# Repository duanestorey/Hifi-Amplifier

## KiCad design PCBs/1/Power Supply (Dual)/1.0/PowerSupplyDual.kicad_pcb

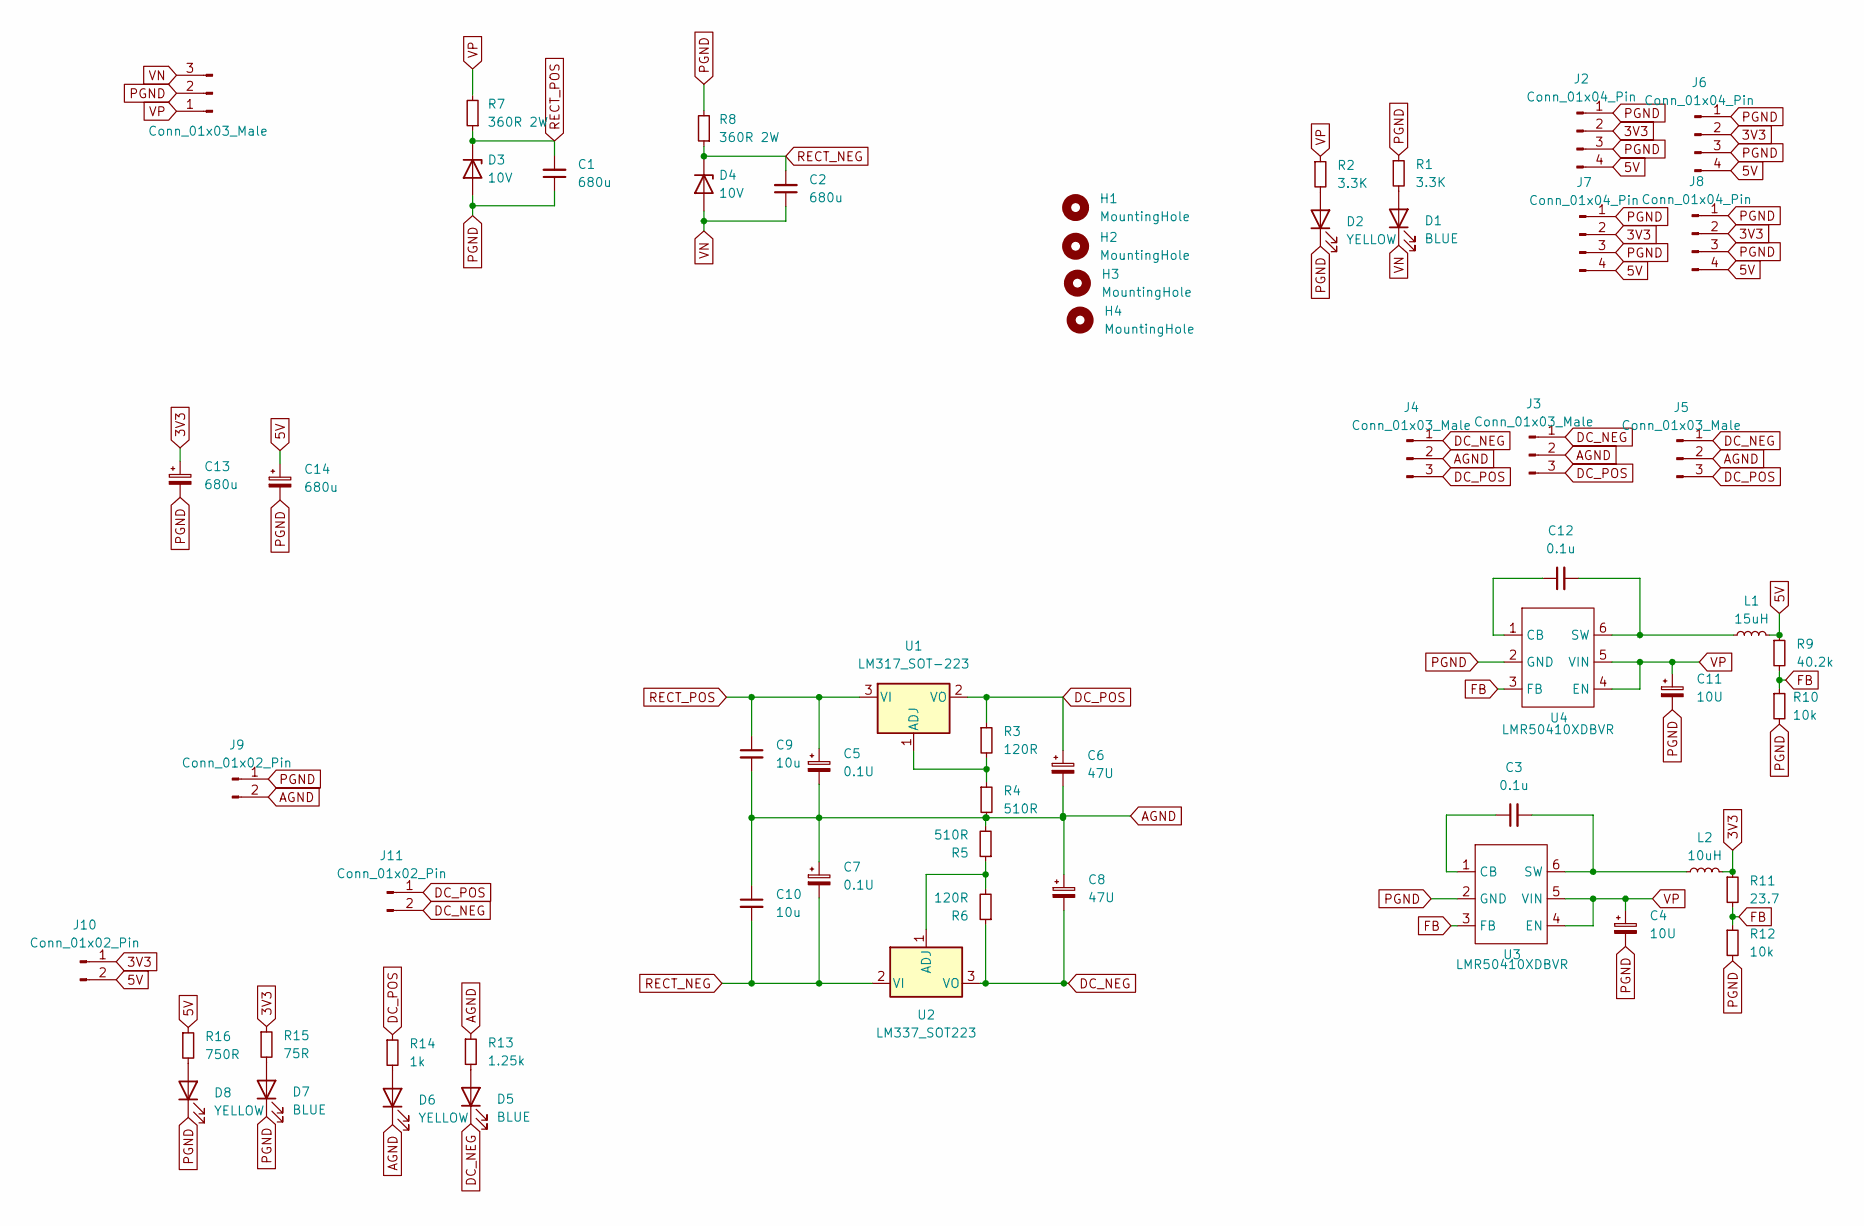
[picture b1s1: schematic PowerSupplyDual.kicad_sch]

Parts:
C1, C2, C13, C14: 680u; CP_Radial_D8.0mm_P5.00mm
C3, C12: 0.1u; C_0805_2012Metric_Pad1.18x1.45mm_HandSolder
C4, C11: 10U; C_1206_3216Metric_Pad1.33x1.80mm_HandSolder
C5, C7: 0.1U; C_0603_1608Metric_Pad1.08x0.95mm_HandSolder
C6, C8: 47U; C_1206_3216Metric_Pad1.33x1.80mm_HandSolder
C9, C10: 10u; C_1206_3216Metric_Pad1.33x1.80mm_HandSolder
D1, D5, D7: BLUE; LED_0805_2012Metric_Pad1.15x1.40mm_HandSolder
D2, D6, D8: YELLOW; LED_0805_2012Metric_Pad1.15x1.40mm_HandSolder
D3, D4: 10V; D_DO-41_SOD81_P10.16mm_Horizontal
H1, H2, H3, H4: MountingHole; MountingHole_3.2mm_M3
J1: Conn_01x03_Male; JST_VH_B3P-VH_1x03_P3.96mm_Vertical
J2, J6, J7, J8: Conn_01x04_Pin; JST_XH_B4B-XH-A_1x04_P2.50mm_Vertical
J3, J4, J5: Conn_01x03_Male; JST_PH_B3B-PH-K_1x03_P2.00mm_Vertical
J9: Conn_01x02_Pin; JST_XH_B2B-XH-A_1x02_P2.50mm_Vertical
J10, J11: Conn_01x02_Pin; PinHeader_1x02_P2.54mm_Vertical
L1: 15uH; L_Taiyo-Yuden_NR-60xx_HandSoldering
L2: 10uH; L_Taiyo-Yuden_NR-60xx_HandSoldering
R1, R2: 3.3K; R_0603_1608Metric_Pad0.98x0.95mm_HandSolder
R3, R6: 120R; R_0603_1608Metric_Pad0.98x0.95mm_HandSolder
R4, R5: 510R; R_0603_1608Metric_Pad0.98x0.95mm_HandSolder
R7, R8: 360R 2W; R_Axial_DIN0411_L9.9mm_D3.6mm_P15.24mm_Horizontal
R9: 40.2k; R_0603_1608Metric_Pad0.98x0.95mm_HandSolder
R10, R12: 10k; R_0603_1608Metric_Pad0.98x0.95mm_HandSolder
R11: 23.7; R_0603_1608Metric_Pad0.98x0.95mm_HandSolder
R13: 1.25k; R_0603_1608Metric_Pad0.98x0.95mm_HandSolder
R14: 1k; R_0603_1608Metric_Pad0.98x0.95mm_HandSolder
R15: 75R; R_0603_1608Metric_Pad0.98x0.95mm_HandSolder
R16: 750R; R_0603_1608Metric_Pad0.98x0.95mm_HandSolder
U1: LM317_SOT-223; SOT-223-3_TabPin2
U2: LM337_SOT223; SOT-223-3_TabPin2
U3, U4: LMR50410XDBVR; SOT-23-6_Handsoldering

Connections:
3V3: C13.1, J2.2, J6.2, J7.2, J8.2, J10.1, L2.2, R11.1, R15.1
5V: C14.1, J2.4, J6.4, J7.4, J8.4, J10.2, L1.2, R9.1, R16.1
AGND: C5.2, C6.2, C7.1, C8.1, C9.2, C10.1, D6.1 (K), J3.2, J4.2, J5.2, J9.2, R4.2, R5.2, R13.1
DC_NEG: C8.2, D5.1 (K), J3.1, J4.1, J5.1, J11.2, R6.1, U2.3 (VO)
DC_POS: C6.1, J3.3, J4.3, J5.3, J11.1, R3.1, R14.1, U1.2 (VO)
FB: R9.2, R10.1, R11.2, R12.1, U3.3 (FB), U4.3 (FB)
unnamed: D1.2 (A), R1.2
unnamed: D2.2 (A), R2.2
unnamed: D5.2 (A), R13.2
unnamed: D6.2 (A), R14.2
unnamed: D7.2 (A), R15.2
unnamed: D8.2 (A), R16.2
unnamed: R3.2, R4.1, U1.1 (ADJ)
unnamed: R5.1, R6.2, U2.1 (ADJ)
unnamed: C3.1, U3.1 (CB)
unnamed: C3.2, L2.1, U3.6 (SW)
unnamed: C12.1, U4.1 (CB)
unnamed: C12.2, L1.1, U4.6 (SW)
PGND: C1.1, C4.2, C11.2, C13.2, C14.2, D2.1 (K), D3.2 (A), D7.1 (K), D8.1 (K), J1.2, J2.1, J2.3, J6.1, J6.3, J7.1, J7.3, J8.1, J8.3, J9.1, R1.1, R8.2, R10.2, R12.2, U3.2 (GND), U4.2 (GND)
RECT_NEG: C2.2, C7.2, C10.2, D4.1 (K), R8.1, U2.2 (VI)
RECT_POS: C1.2, C5.1, C9.1, D3.1 (K), R7.1, U1.3 (VI)
VN: C2.1, D1.1 (K), D4.2 (A), J1.3
VP: C4.1, C11.1, J1.1, R2.1, R7.2, U3.4 (EN), U3.5 (VIN), U4.4 (EN), U4.5 (VIN)

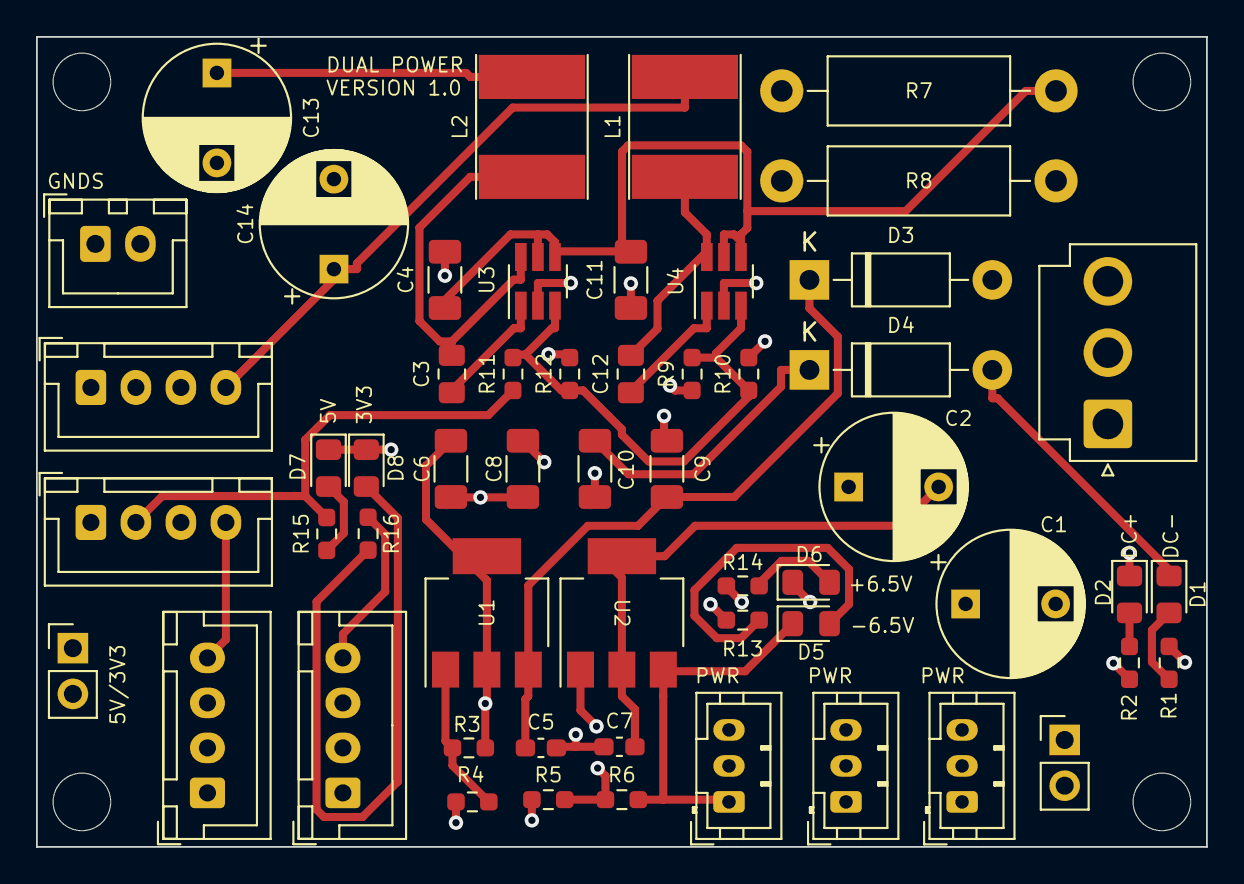
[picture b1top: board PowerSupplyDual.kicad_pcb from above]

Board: 4 copper layers, 65.0 x 45.0 mm, 59 parts (0 on the bottom side), 23 nets.

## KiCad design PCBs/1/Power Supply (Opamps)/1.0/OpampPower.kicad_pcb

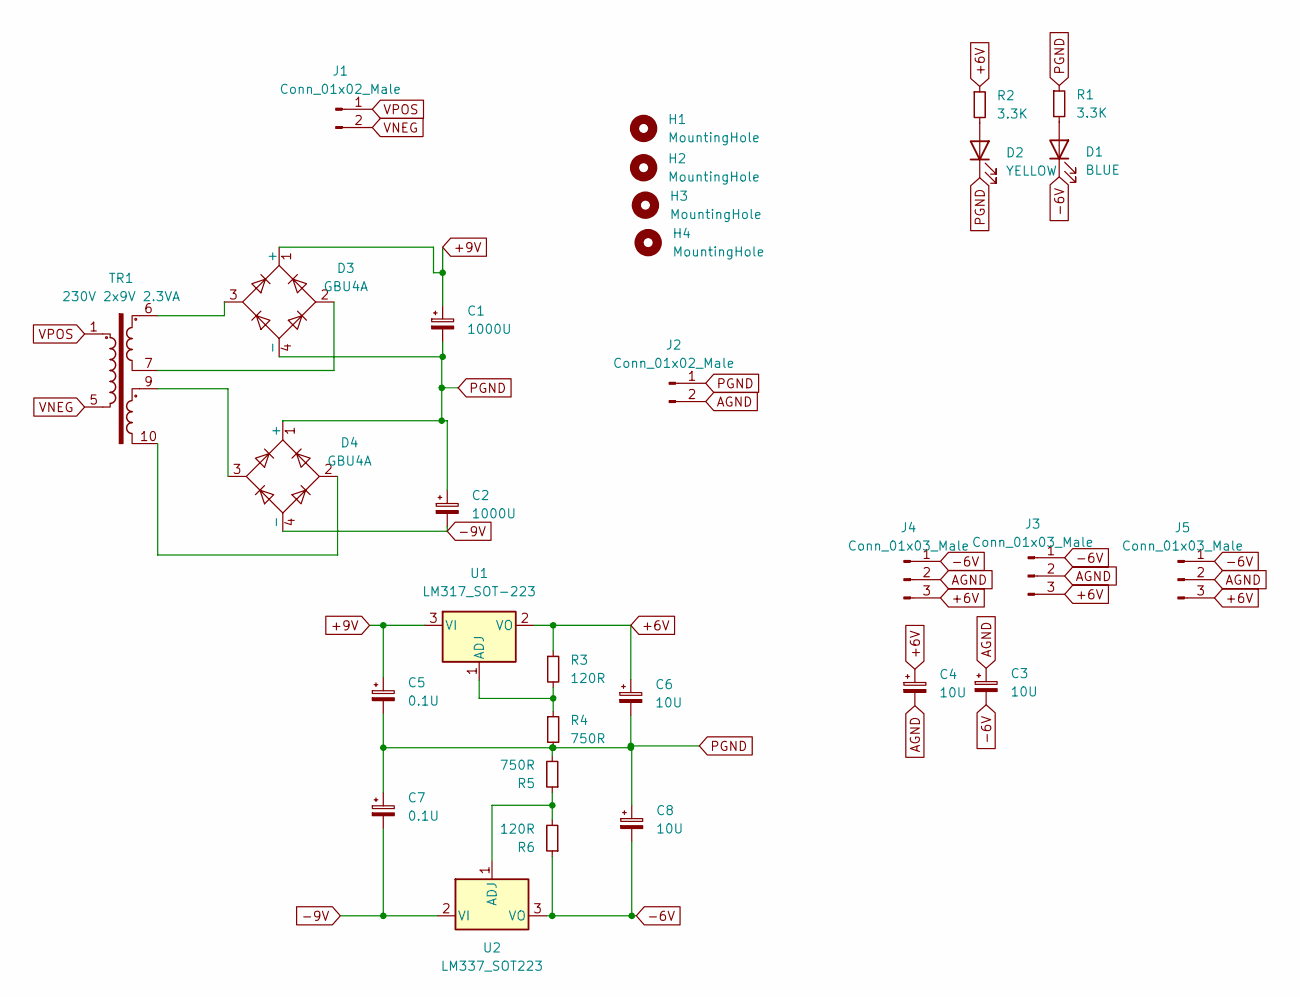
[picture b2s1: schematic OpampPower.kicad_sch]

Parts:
C1, C2: 1000U; CP_Radial_D10.0mm_P5.00mm_P7.50mm
C3, C4, C6, C8: 10U; C_1206_3216Metric_Pad1.33x1.80mm_HandSolder
C5, C7: 0.1U; C_0603_1608Metric_Pad1.08x0.95mm_HandSolder
D1: BLUE; LED_0805_2012Metric_Pad1.15x1.40mm_HandSolder
D2: YELLOW; LED_0805_2012Metric_Pad1.15x1.40mm_HandSolder
D3, D4: GBU4A; Diode_Bridge_Vishay_GBU
H1, H2, H3, H4: MountingHole; MountingHole_3.2mm_M3
J1: Conn_01x02_Male; JST_XH_B2B-XH-A_1x02_P2.50mm_Vertical
J2: Conn_01x02_Male; JST_PH_B2B-PH-K_1x02_P2.00mm_Vertical
J3, J4, J5: Conn_01x03_Male; JST_PH_B3B-PH-K_1x03_P2.00mm_Vertical
R1, R2: 3.3K; R_0603_1608Metric_Pad0.98x0.95mm_HandSolder
R3, R6: 120R; R_0805_2012Metric_Pad1.20x1.40mm_HandSolder
R4, R5: 750R; R_0805_2012Metric_Pad1.20x1.40mm_HandSolder
TR1: 230V 2x9V 2.3VA; Transformer_Breve_TEZ-28x33
U1: LM317_SOT-223; SOT-223-3_TabPin2
U2: LM337_SOT223; SOT-223-3_TabPin2

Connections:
+6V: C4.1, C6.1, J3.3, J4.3, J5.3, R2.1, R3.1, U1.2 (VO)
+9V: C1.1, C5.1, D3.1 (+), U1.3 (VI)
-6V: C3.2, C8.2, D1.1 (K), J3.1, J4.1, J5.1, R6.1, U2.3 (VO)
-9V: C2.2, C7.2, D4.4 (-), U2.2 (VI)
AGND: C3.1, C4.2, J2.2, J3.2, J4.2, J5.2
unnamed: D1.2 (A), R1.2
unnamed: D2.2 (A), R2.2
unnamed: D3.2, TR1.7
unnamed: D3.3, TR1.6
unnamed: D4.2, TR1.10
unnamed: D4.3, TR1.9
unnamed: R3.2, R4.1, U1.1 (ADJ)
unnamed: R5.1, R6.2, U2.1 (ADJ)
PGND: C1.2, C2.1, C5.2, C6.2, C7.1, C8.1, D2.1 (K), D3.4 (-), D4.1 (+), J2.1, R1.1, R4.2, R5.2
VNEG: J1.2, TR1.5
VPOS: J1.1, TR1.1

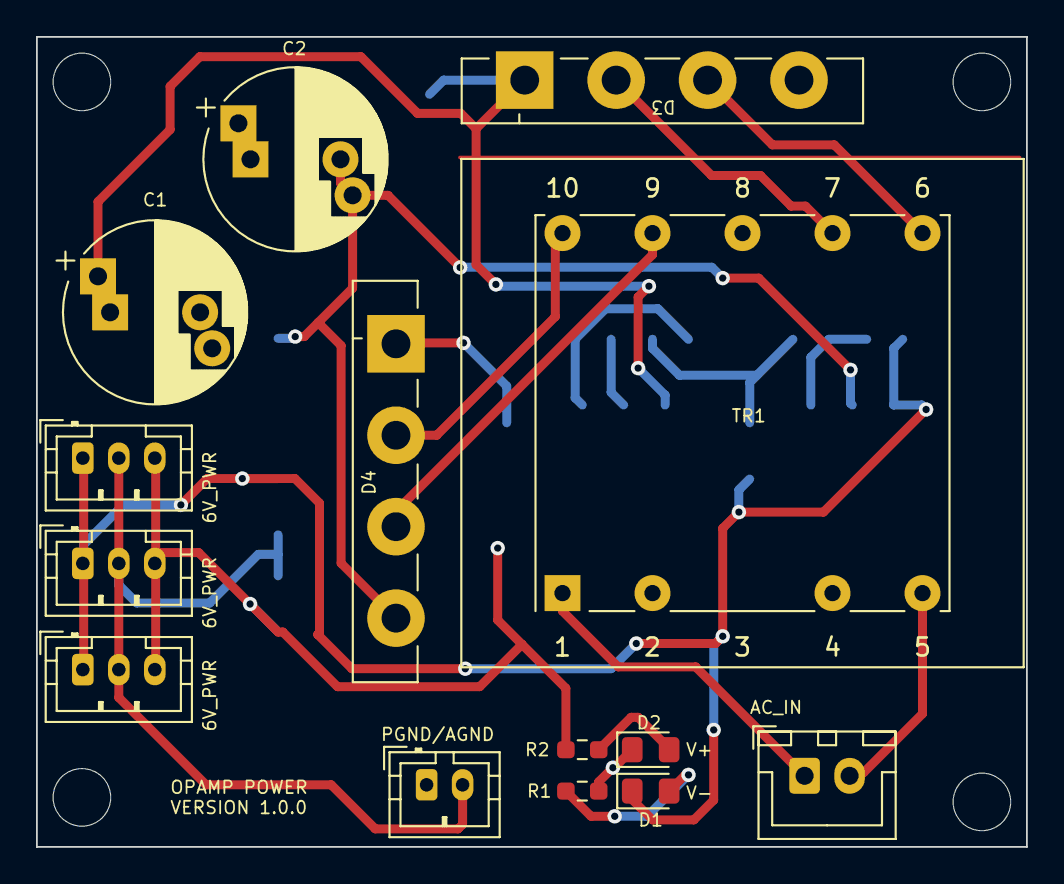
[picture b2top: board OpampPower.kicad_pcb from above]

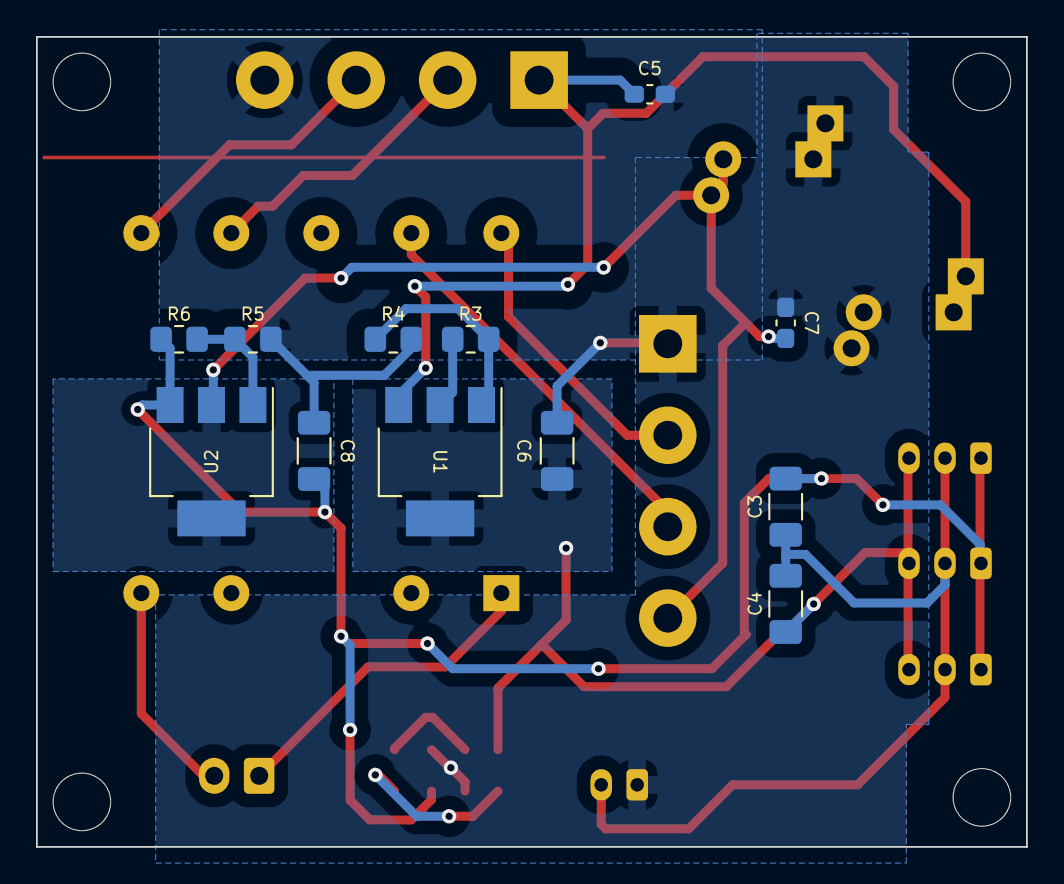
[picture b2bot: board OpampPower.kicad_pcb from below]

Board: 2 copper layers, 55.0 x 45.0 mm, 30 parts (12 on the bottom side), 16 nets.

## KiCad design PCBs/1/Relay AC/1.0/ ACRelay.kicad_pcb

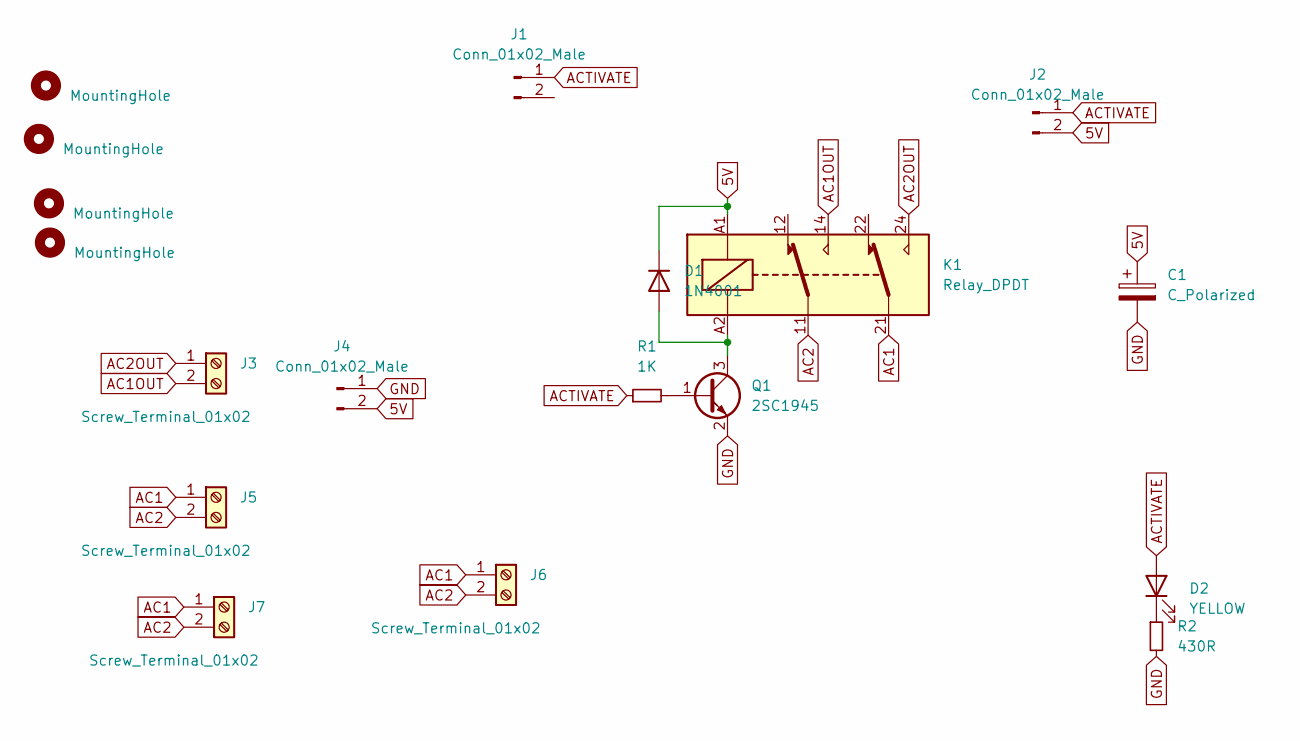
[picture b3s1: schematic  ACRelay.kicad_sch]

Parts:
C1: C_Polarized; CP_Radial_D6.3mm_P2.50mm
D1: 1N4001; D_SMA
D2: YELLOW; D_0805_2012Metric_Pad1.15x1.40mm_HandSolder
H1, H2, H3, H4: MountingHole; MountingHole_3.2mm_M3
J1, J4: Conn_01x02_Male; JST_PH_B2B-PH-K_1x02_P2.00mm_Vertical
J2: Conn_01x02_Male; PinHeader_1x02_P2.54mm_Vertical
J3, J5, J6, J7: Screw_Terminal_01x02; JST_XH_B2B-XH-A_1x02_P2.50mm_Vertical
K1: Relay_DPDT; Relay_DPDT_Omron_G2RL-2
Q1: 2SC1945; SOT-23_Handsoldering
R1: 1K; R_0603_1608Metric
R2: 430R; R_0603_1608Metric_Pad0.98x0.95mm_HandSolder

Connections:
5V: C1.1, D1.1 (K), J2.2, J4.2, K1.A1
AC1: J5.1, J6.1, J7.1, K1.21
AC1OUT: J3.2, K1.14
AC2: J5.2, J6.2, J7.2, K1.11
AC2OUT: J3.1, K1.24
ACTIVATE: D2.2 (A), J1.1, J2.1, R1.1
GND: C1.2, J4.1, Q1.2 (E), R2.2
unnamed: D1.2 (A), K1.A2, Q1.3 (C)
unnamed: D2.1 (K), R2.1
unnamed: Q1.1 (B), R1.2

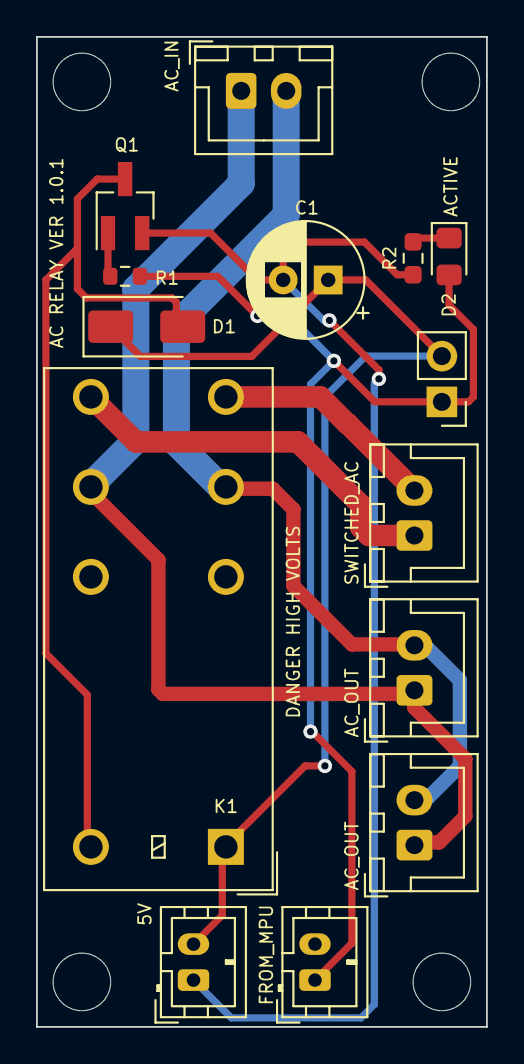
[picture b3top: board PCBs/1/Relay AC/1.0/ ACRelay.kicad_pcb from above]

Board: 2 copper layers, 25.0 x 55.0 mm, 18 parts (0 on the bottom side), 10 nets.

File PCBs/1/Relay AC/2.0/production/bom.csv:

Designator,Footprint,Quantity,Value,LCSC Part #
C1,CP_Radial_D6.3mm_P2.50mm,1,C_Polarized,
D1,D_SMA,1,1N4001,
D2,D_0805_2012Metric_Pad1.15x1.40mm_HandSolder,1,YELLOW,
"H1, H2, H3, H4",MountingHole_3.2mm_M3,4,MountingHole,
"J1, J4",JST_PH_B2B-PH-K_1x02_P2.00mm_Vertical,2,Conn_01x02_Male,
J2,PinHeader_1x02_P2.54mm_Vertical,1,Conn_01x02_Male,
"J3, J5, J6, J7",JST_XH_B2B-XH-A_1x02_P2.50mm_Vertical,4,Screw_Terminal_01x02,
Q1,SOT-23_Handsoldering,1,2SC1945,
R1,R_0603_1608Metric,1,1K,
R2,R_0603_1608Metric_Pad0.98x0.95mm_HandSolder,1,430R,
RL1,Relay_DPDT_Omron_G2RL,1,G2RL-2-ASI-DC5,

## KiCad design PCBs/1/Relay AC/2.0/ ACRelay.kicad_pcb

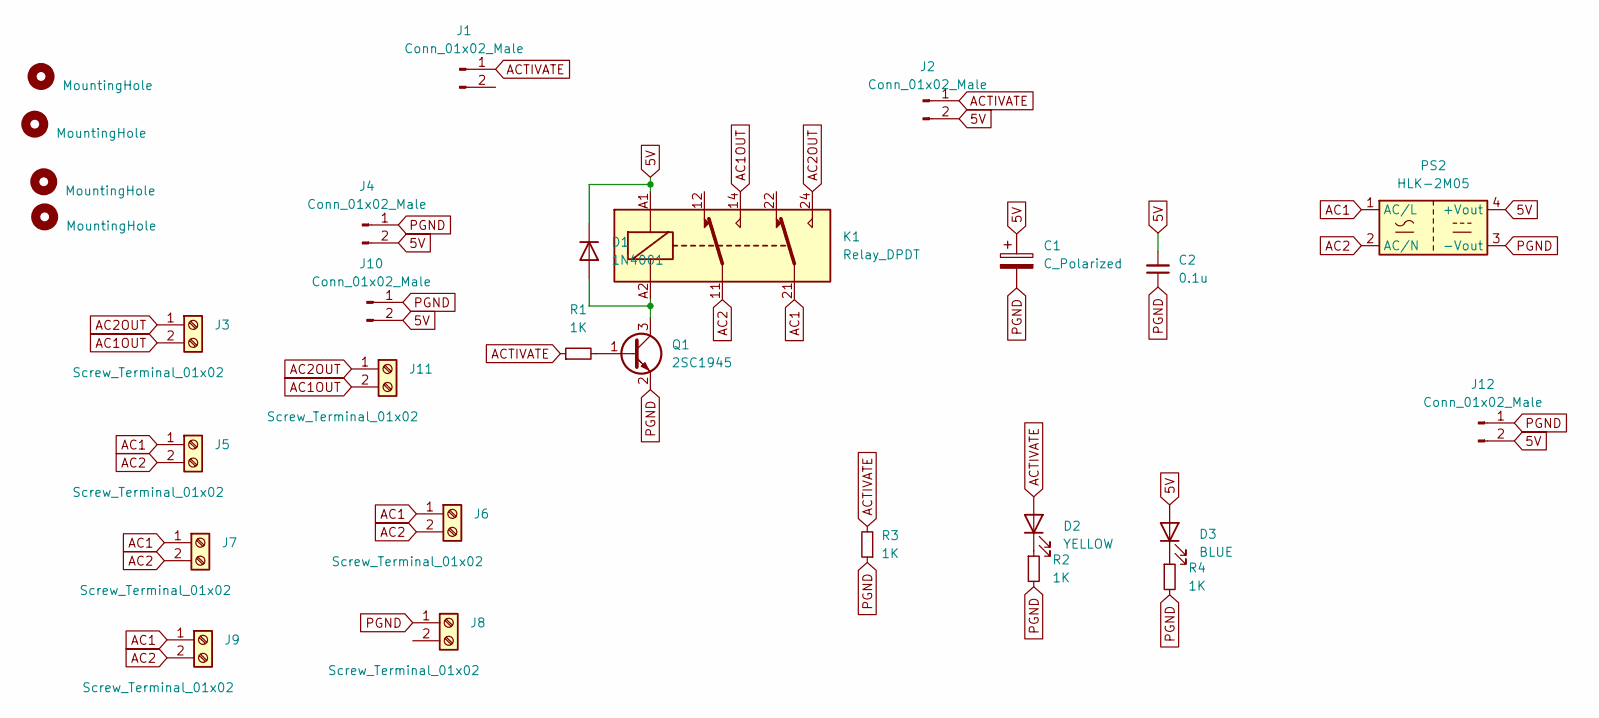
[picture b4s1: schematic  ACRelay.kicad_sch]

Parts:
C1: C_Polarized; CP_Radial_D8.0mm_P2.50mm
C2: 0.1u; C_0805_2012Metric_Pad1.18x1.45mm_HandSolder
D1: 1N4001; D_SMA
D2: YELLOW; D_0805_2012Metric_Pad1.15x1.40mm_HandSolder
D3: BLUE; D_0805_2012Metric_Pad1.15x1.40mm_HandSolder
H1, H2, H3, H4: MountingHole; MountingHole_3.2mm_M3
J1, J4, J10: Conn_01x02_Male; JST_PH_B2B-PH-K_1x02_P2.00mm_Vertical
J2, J12: Conn_01x02_Male; PinHeader_1x02_P2.54mm_Vertical
J3, J5, J6, J7, J8, J9, J11: Screw_Terminal_01x02; JST_XH_B2B-XH-A_1x02_P2.50mm_Vertical
K1: Relay_DPDT; Relay_DPDT_Omron_G2RL-2
PS2: HLK-2M05
Q1: 2SC1945; SOT-23_Handsoldering
R1, R3: 1K; R_0603_1608Metric
R2, R4: 1K; R_0603_1608Metric_Pad0.98x0.95mm_HandSolder

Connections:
5V: C1.1, C2.2, D1.1 (K), D3.2 (A), J2.2, J4.2, J10.2, J12.2, K1.A1, PS2.4 (+Vout)
AC1: J5.1, J6.1, J7.1, J9.1, K1.21, PS2.1 (AC/L)
AC1OUT: J3.2, J11.2, K1.14
AC2: J5.2, J6.2, J7.2, J9.2, K1.11, PS2.2 (AC/N)
AC2OUT: J3.1, J11.1, K1.24
ACTIVATE: D2.2 (A), J1.1, J2.1, R1.1, R3.2
unnamed: D1.2 (A), K1.A2, Q1.3 (C)
unnamed: D2.1 (K), R2.1
unnamed: D3.1 (K), R4.1
unnamed: Q1.1 (B), R1.2
PGND: C1.2, C2.1, J4.1, J8.1, J10.1, J12.1, PS2.3 (-Vout), Q1.2 (E), R2.2, R3.1, R4.2

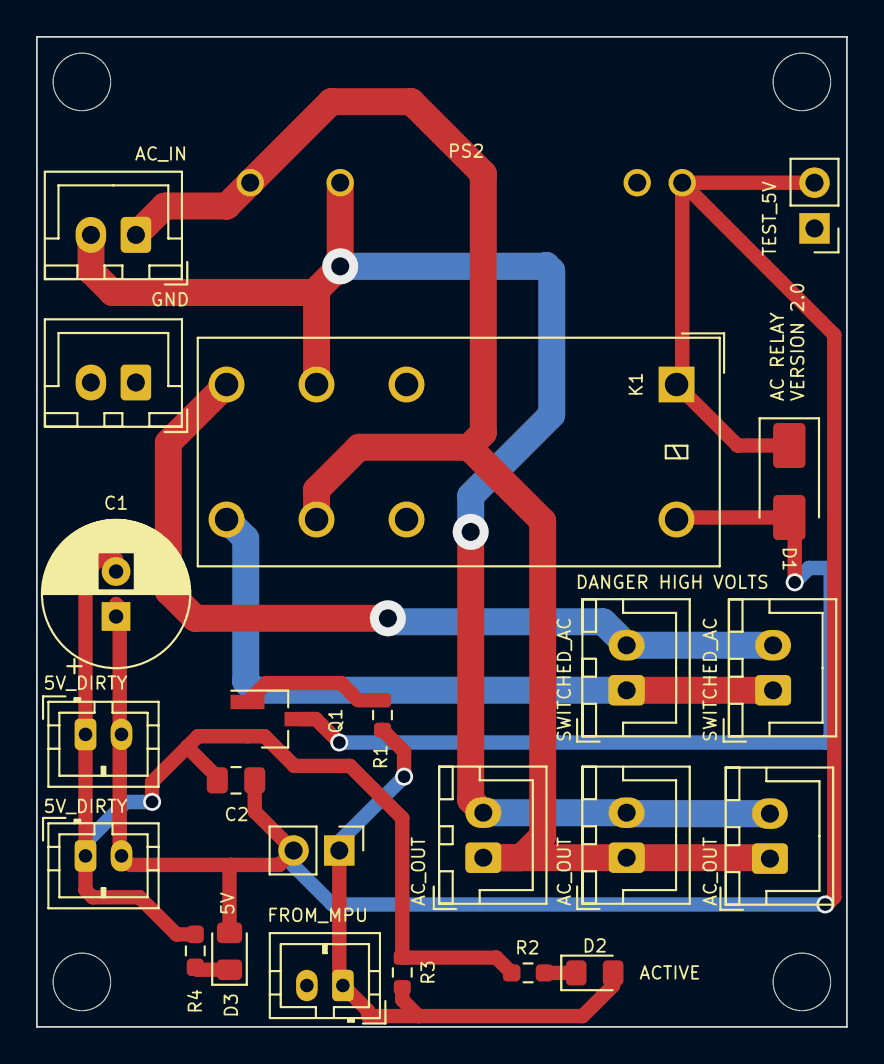
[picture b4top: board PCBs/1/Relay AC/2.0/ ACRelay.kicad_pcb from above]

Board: 2 copper layers, 45.0 x 55.0 mm, 28 parts (0 on the bottom side), 11 nets.

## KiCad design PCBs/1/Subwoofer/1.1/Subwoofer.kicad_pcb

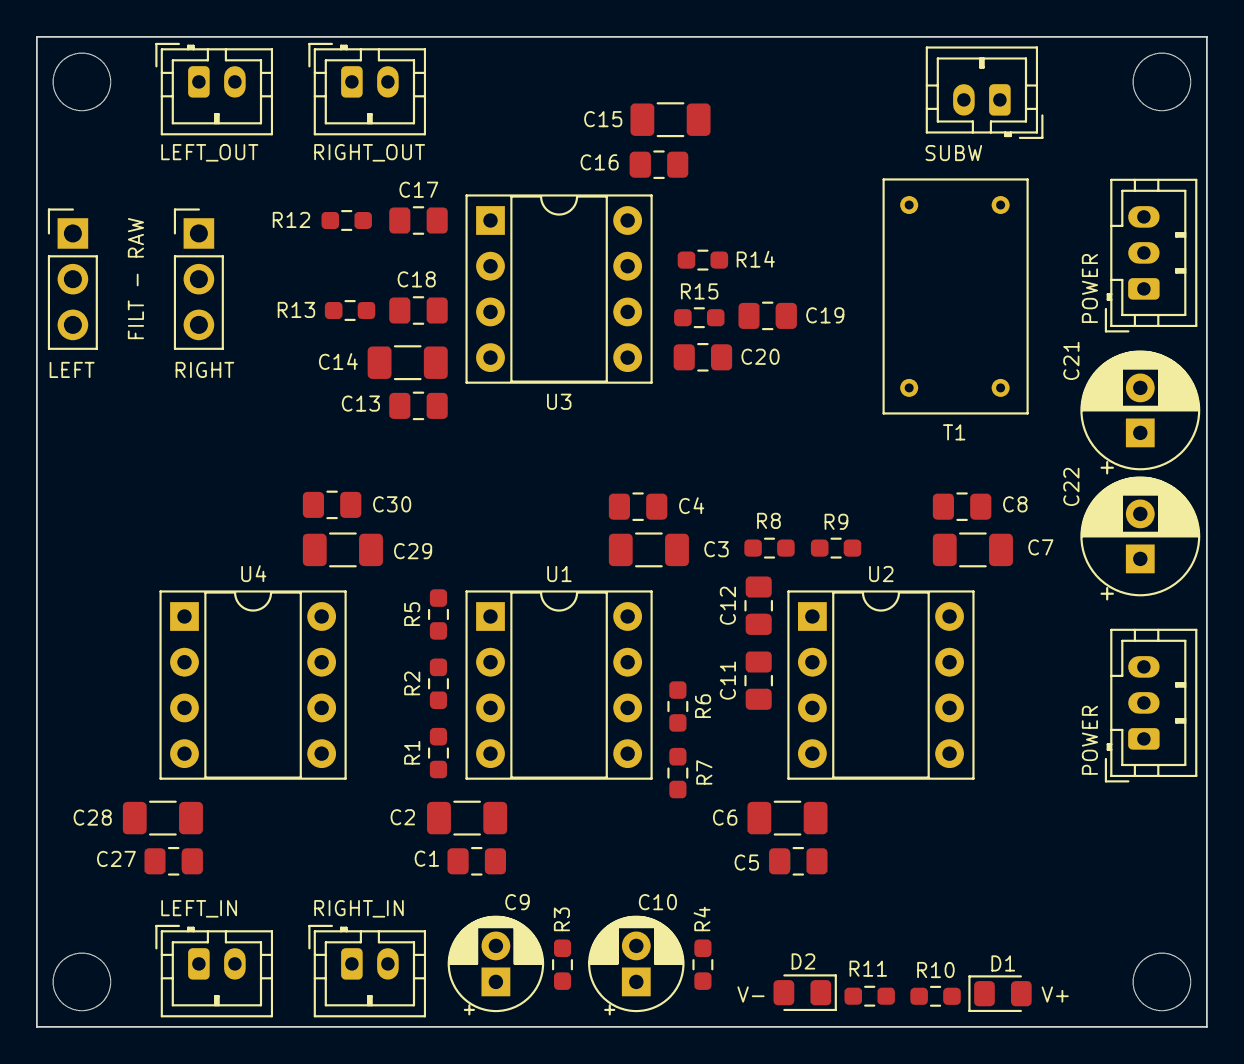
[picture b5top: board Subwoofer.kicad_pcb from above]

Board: 2 copper layers, 65.0 x 55.0 mm, 61 parts (0 on the bottom side), 31 nets, no tracks yet.

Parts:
C1, C4, C5, C8, C13, C16, C27, C30: 0.1U; C_0805_2012Metric_Pad1.18x1.45mm_HandSolder
C2, C3, C6, C7, C14, C15, C28, C29: 10U; C_1206_3216Metric_Pad1.33x1.80mm_HandSolder
C9, C10: 10u; CP_Radial_D5.0mm_P2.00mm
C11, C18, C20: 56n C0G; C_0805_2012Metric_Pad1.18x1.45mm_HandSolder
C12, C17, C19: 130n C0G; C_0805_2012Metric_Pad1.18x1.45mm_HandSolder
C21, C22: 470u; CP_Radial_D6.3mm_P2.50mm
D1: YELLOW; LED_0805_2012Metric_Pad1.15x1.40mm_HandSolder
D2: BLUE; LED_0805_2012Metric_Pad1.15x1.40mm_HandSolder
H1, H2, H3, H4: MountingHole; MountingHole_3.2mm_M3
J1, J2, J4, J7, J15: Conn_01x02_Pin; JST_PH_B2B-PH-K_1x02_P2.00mm_Vertical
J3, J9: Conn_01x03_Male; JST_PH_B3B-PH-K_1x03_P2.00mm_Vertical
J5, J6: Conn_01x03_Pin; PinHeader_1x03_P2.54mm_Vertical
R1, R2, R3, R4, R6, R7: 10K; R_0603_1608Metric_Pad0.98x0.95mm_HandSolder
R5: 20K; R_0603_1608Metric_Pad0.98x0.95mm_HandSolder
R8, R13, R15: 23K; R_0603_1608Metric_Pad0.98x0.95mm_HandSolder
R9, R12, R14: 10.5K; R_0603_1608Metric_Pad0.98x0.95mm_HandSolder
R10: 1.25K; R_0603_1608Metric_Pad0.98x0.95mm_HandSolder
R11: 1K; R_0603_1608Metric_Pad0.98x0.95mm_HandSolder
T1: Transformer_Audio; DA101C
U1, U2, U3, U4: OPA2134; DIP-8_W7.62mm_Socket

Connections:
AGND: C1.2, C2.2, C3.2, C4.2, C5.2, C6.2, C7.2, C8.2, C11.2, C13.2, C14.2, C15.2, C16.2, C18.2, C20.2, C21.1, C22.2, C27.2, C28.2, C29.2, C30.2, D2.2 (A), J1.1, J2.1, J3.2, J4.1, J9.2, J15.1, R3.1, R4.1, R10.1, T1.2 (AB), U2.5 (InB+)
COMBINED: R7.2, R9.2, U1.7 (OutB)
LEFT_BUF: R1.2, R12.2, U4.1 (OutA), U4.2 (InA-)
LEFT_FILT: C17.2, J5.3, U3.1 (OutA), U3.2 (InA-)
LEFT_IN: C9.1, J4.2, J5.1, U4.3 (InA+)
LEFT_OUT: J1.2, J5.2
unnamed: C9.2, R3.2
unnamed: C10.2, R4.2
unnamed: C12.1, R8.2, R9.1
unnamed: C17.1, R12.1, R13.2
unnamed: C19.2, R14.1, R15.2
unnamed: D1.1 (K), R10.2
unnamed: D2.1 (K), R11.2
unnamed: R5.2, U1.3 (InA+)
unnamed: R1.1, R2.1, U1.2 (InA-)
unnamed: R7.1, U1.5 (InB+)
unnamed: R6.2, U1.6 (InB-)
unnamed: R5.1, R6.1, U1.1 (OutA)
unnamed: C11.1, R8.1, U2.3 (InA+)
unnamed: U2.6 (InB-), U2.7 (OutB)
unnamed: C18.1, R13.1, U3.3 (InA+)
unnamed: C20.1, R15.1, U3.5 (InB+)
RIGHT_BUF: R2.2, R14.2, U4.6 (InB-), U4.7 (OutB)
RIGHT_FILT: C19.1, J6.3, U3.6 (InB-), U3.7 (OutB)
RIGHT_IN: C10.1, J6.1, J15.2, U4.5 (InB+)
RIGHT_OUT: J2.2, J6.2
SUBW: C12.2, T1.1 (AA), U2.1 (OutA), U2.2 (InA-)
SUBWN: J7.1, T1.3 (SA)
SUBWP: J7.2, T1.4 (SB)
V+: C3.1, C4.1, C7.1, C8.1, C15.1, C16.1, C22.1, C29.1, C30.1, D1.2 (A), J3.3, J9.3, U1.8 (V+), U2.8 (V+), U3.8 (V+), U4.8 (V+)
V-: C1.1, C2.1, C5.1, C6.1, C13.1, C14.1, C21.2, C27.1, C28.1, J3.1, J9.1, R11.1, U1.4 (V-), U2.4 (V-), U3.4 (V-), U4.4 (V-)
